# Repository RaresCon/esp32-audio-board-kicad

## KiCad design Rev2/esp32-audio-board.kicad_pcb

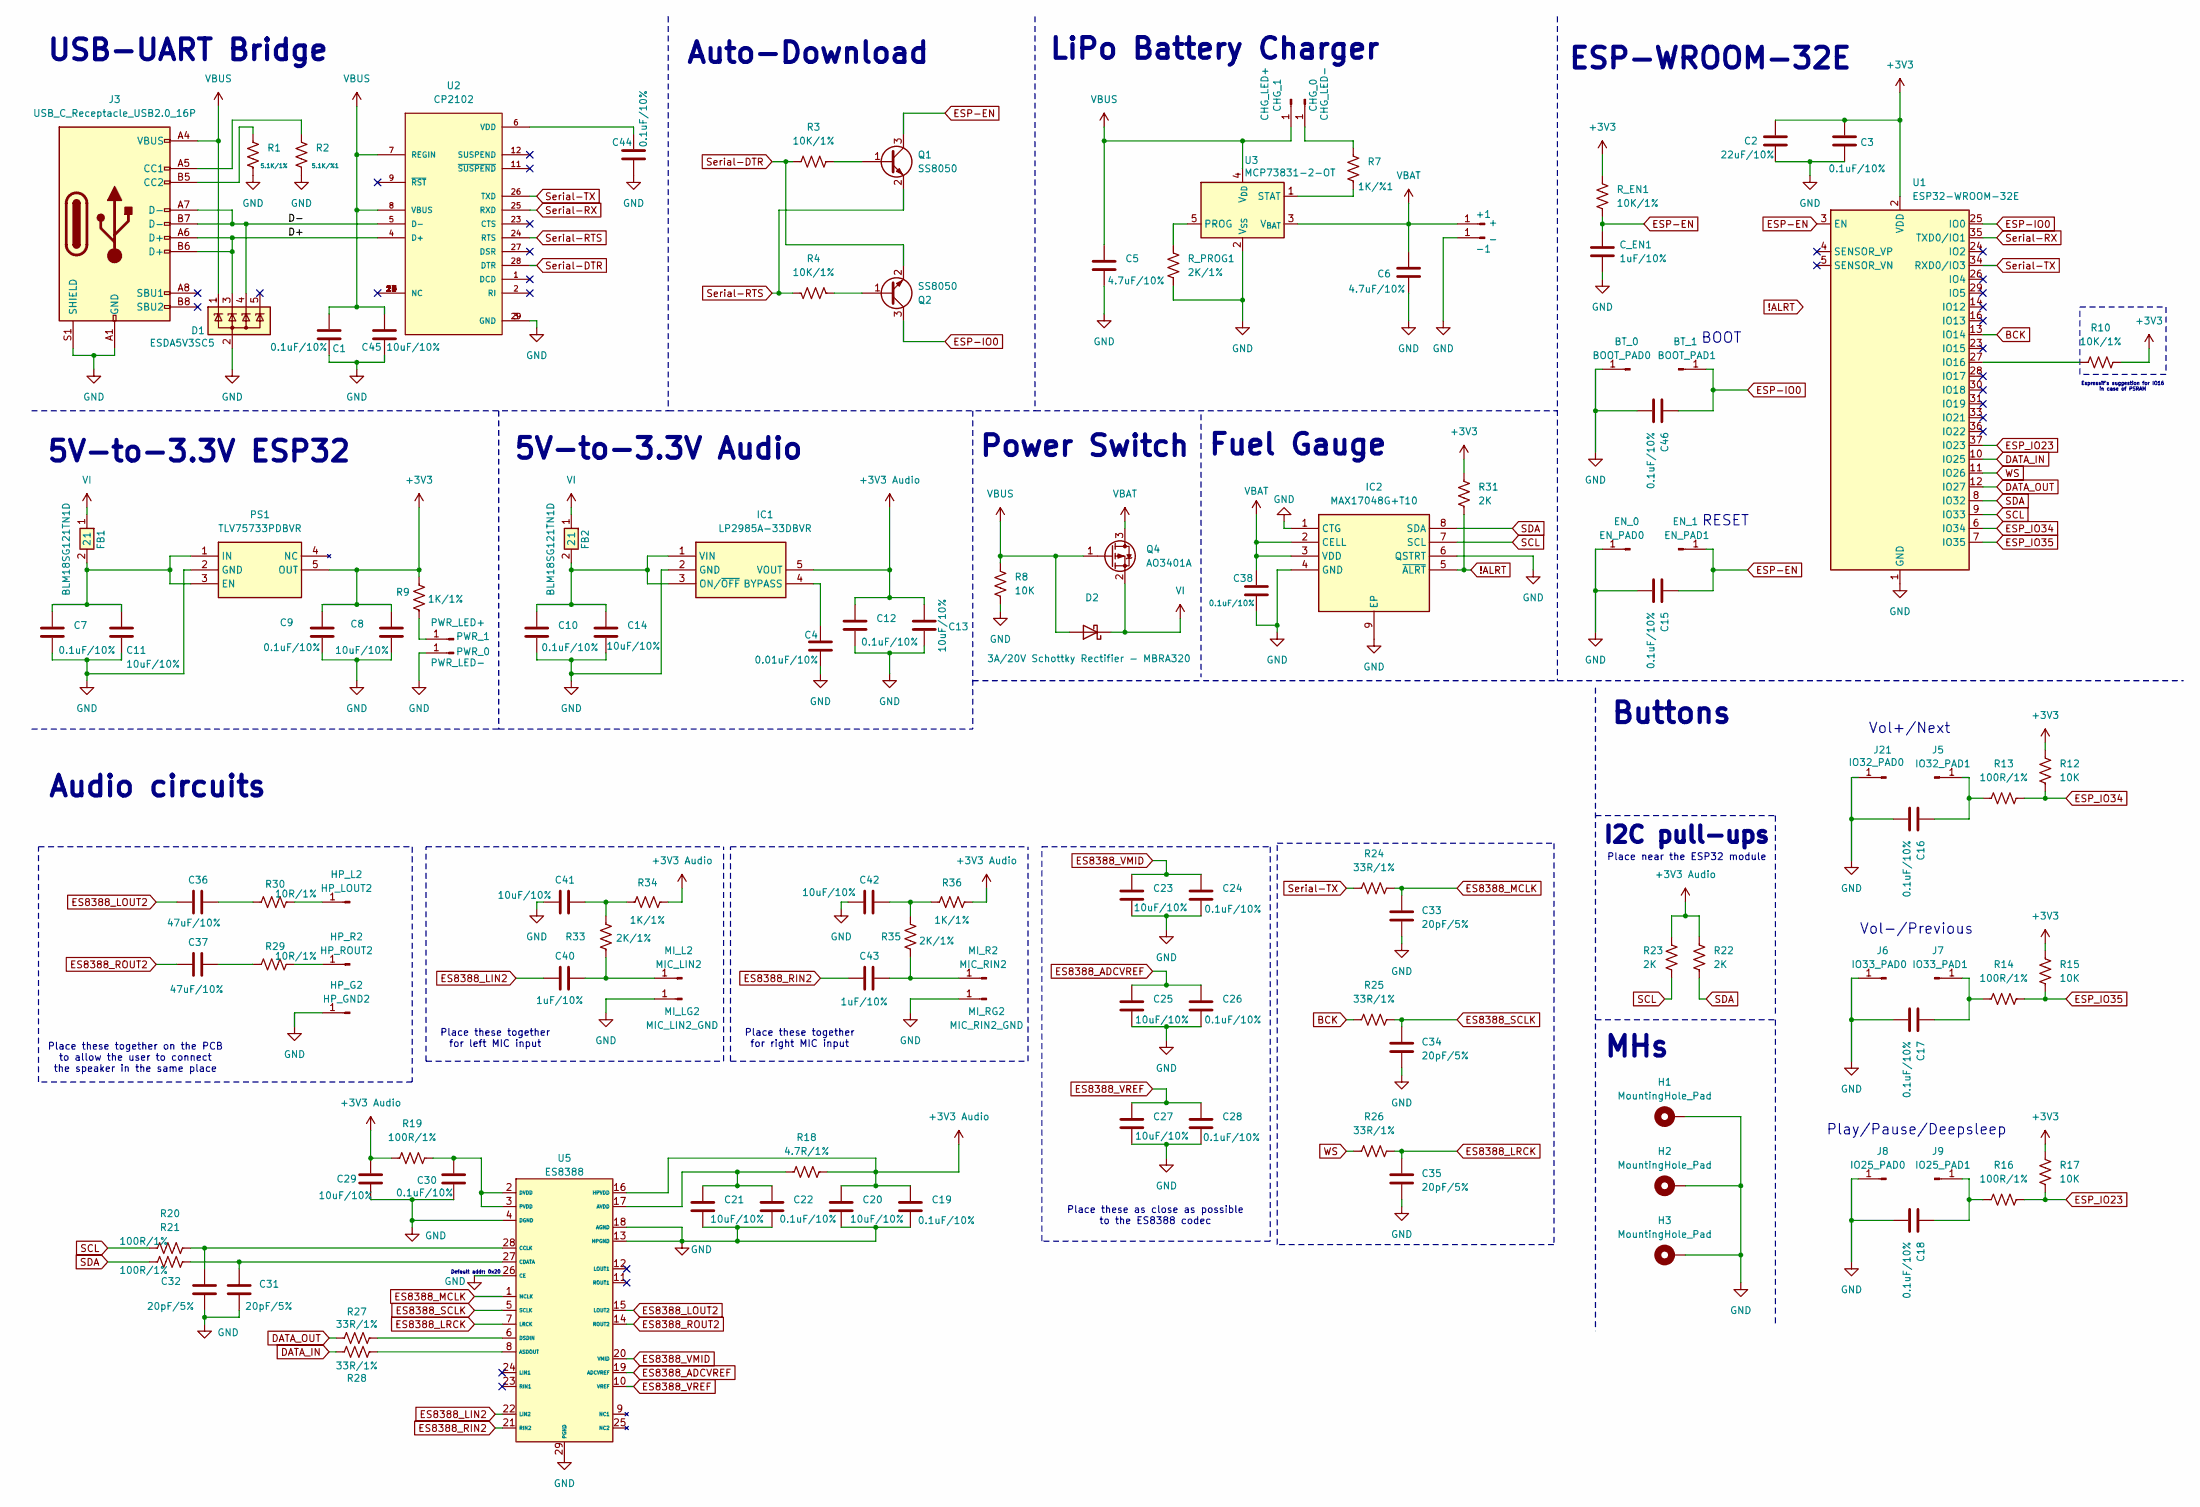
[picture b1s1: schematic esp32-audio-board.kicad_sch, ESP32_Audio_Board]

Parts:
+1: +; SolderPad_SMD_2x2mm
-1: -; SolderPad_SMD_2x2mm
BT_0: BOOT_PAD0; SolderPad_SMD_1x1mm
BT_1: BOOT_PAD1; SolderPad_SMD_1x1mm
C1, C3, C7, C9, C10, C12, C15, C16, C17, C18, C19, C22, C24, C26, C28, C30, C38, C44, C46: 0.1uF/10%; C_0402_1005Metric_Pad0.74x0.62mm_HandSolder
C2: 22uF/10%; C_0402_1005Metric_Pad0.74x0.62mm_HandSolder
C4: 0.01uF/10%; C_0402_1005Metric_Pad0.74x0.62mm_HandSolder
C5, C6: 4.7uF/10%; C_0402_1005Metric_Pad0.74x0.62mm_HandSolder
C8, C11, C13, C14, C20, C21, C23, C25, C27, C29, C41, C42, C45: 10uF/10%; C_0402_1005Metric_Pad0.74x0.62mm_HandSolder
C31, C32, C33, C34, C35: 20pF/5%; C_0402_1005Metric_Pad0.74x0.62mm_HandSolder
C36, C37: 47uF/10%; C_0402_1005Metric_Pad0.74x0.62mm_HandSolder
C40, C43: 1uF/10%; C_0402_1005Metric_Pad0.74x0.62mm_HandSolder
CHG_0: CHG_LED-; SolderPad_SMD_1x1mm
CHG_1: CHG_LED+; SolderPad_SMD_1x1mm
C_EN1: 1uF/10%; C_0402_1005Metric_Pad0.74x0.62mm_HandSolder
D1: ESDA5V3SC5; SOT-23-5_HandSoldering
D2: 3A/20V Schottky Rectifier - MBRA320; D_SMA
EN_0: EN_PAD0; SolderPad_SMD_1x1mm
EN_1: EN_PAD1; SolderPad_SMD_1x1mm
FB1, FB2: BLM18SG121TN1D; BLM18EG101TH1D; Mouser Part Number 81-BLM18SG121TN1D
H1, H2, H3: MountingHole_Pad; MountingHole_2.2mm_M2_Pad_TopOnly
HP_G2: HP_GND2; SolderPad_SMD_1x2mm
HP_L2: HP_LOUT2; SolderPad_SMD_1x2mm
HP_R2: HP_ROUT2; SolderPad_SMD_1x2mm
IC1: LP2985A-33DBVR; SOT95P280X145-5N; Mouser Part Number 595-LP2985A-33DBVR
IC2: MAX17048G+T10; SON50P200X200X80-9N-D; Mouser Part Number 700-MAX17048G+T10
J3: USB_C_Receptacle_USB2.0_16P; USB_C_Receptacle_GCT_USB4105-xx-A_16P_TopMnt_Horizontal
J5: IO32_PAD1; SolderPad_SMD_1x1mm
J6: IO33_PAD0; SolderPad_SMD_1x1mm
J7: IO33_PAD1; SolderPad_SMD_1x1mm
J8: IO25_PAD0; SolderPad_SMD_1x1mm
J9: IO25_PAD1; SolderPad_SMD_1x1mm
J21: IO32_PAD0; SolderPad_SMD_1x1mm
MI_L2: MIC_LIN2; SolderPad_SMD_1x2mm
MI_LG2: MIC_LIN2_GND; SolderPad_SMD_1x2mm
MI_R2: MIC_RIN2; SolderPad_SMD_1x2mm
MI_RG2: MIC_RIN2_GND; SolderPad_SMD_1x2mm
PS1: TLV75733PDBVR; SOT95P280X145-5N; Mouser Part Number 595-TLV75733PDBVR
PWR_0: PWR_LED-; SolderPad_SMD_1x1mm
PWR_1: PWR_LED+; SolderPad_SMD_1x1mm
Q1, Q2: SS8050; SOT-23
Q4: AO3401A; SOT-23
R1: 5.1K/1%; R_0402_1005Metric_Pad0.72x0.64mm_HandSolder
R2: 5.1K/%1; R_0402_1005Metric_Pad0.72x0.64mm_HandSolder
R3, R4, R10: 10K/1%; R_0402_1005Metric_Pad0.72x0.64mm_HandSolder
R7: 1K/%1; R_0402_1005Metric_Pad0.72x0.64mm_HandSolder
R8, R12, R15, R17: 10K; R_0402_1005Metric_Pad0.72x0.64mm_HandSolder
R9, R34, R36: 1K/1%; R_0402_1005Metric_Pad0.72x0.64mm_HandSolder
R13, R14, R16, R19, R20, R21: 100R/1%; R_0402_1005Metric_Pad0.72x0.64mm_HandSolder
R18: 4.7R/1%; R_0402_1005Metric_Pad0.72x0.64mm_HandSolder
R22, R23, R31: 2K; R_0402_1005Metric_Pad0.72x0.64mm_HandSolder
R24, R25, R26, R27, R28: 33R/1%; R_0402_1005Metric_Pad0.72x0.64mm_HandSolder
R29, R30: 10R/1%; R_0402_1005Metric_Pad0.72x0.64mm_HandSolder
R33, R35: 2K/1%; R_0402_1005Metric_Pad0.72x0.64mm_HandSolder
R_EN1: 10K/1%; R_0402_1005Metric_Pad0.72x0.64mm_HandSolder
R_PROG1: 2K/1%; R_0402_1005Metric_Pad0.72x0.64mm_HandSolder
U1: ESP32-WROOM-32E
U2: CP2102; QFN50P500X500X100-29N
U3: MCP73831-2-OT; SOT-23-5
U5: ES8388; QFN-28-1EP_4x4mm_P0.45mm_EP2.6x2.6mm

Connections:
!ALRT: IC2.5 (~ALRT), R31.2
+3V3: C2.1, C3.1, C8.1, C9.1, PS1.5 (OUT), R9.2, R10.2, R12.2, R15.2, R17.2, R31.1, R_EN1.1, U1.2 (VDD)
+3V3 Audio: C12.1, C13.1, C19.1, C20.1, C29.1, IC1.5 (VOUT), R18.2, R19.1, R22.1, R23.1, R34.2, R36.2, U5.16 (HPVDD)
/D+: D1.3 (K), J3.A6 (D+), J3.B6 (D+), U2.4 (D+)
/D-: D1.4 (K), J3.A7 (D-), J3.B7 (D-), U2.5 (D-)
BCK: R25.1, U1.13 (IO14)
DATA_IN: R28.1, U1.10 (IO25)
DATA_OUT: R27.1, U1.12 (IO27)
ES8388_ADCVREF: C25.1, C26.1, U5.19 (ADCVREF)
ES8388_LIN2: C40.1, U5.22 (LIN2)
ES8388_LOUT2: C36.1, U5.15 (LOUT2)
ES8388_LRCK: C35.1, R26.2, U5.7 (LRCK)
ES8388_MCLK: C33.1, R24.2, U5.1 (MCLK)
ES8388_RIN2: C43.1, U5.21 (RIN2)
ES8388_ROUT2: C37.1, U5.14 (ROUT2)
ES8388_SCLK: C34.1, R25.2, U5.5 (SCLK)
ES8388_VMID: C23.1, C24.1, U5.20 (VMID)
ES8388_VREF: C27.1, C28.1, U5.10 (VREF)
ESP-EN: C15.1, C_EN1.1, EN_1.1 (Pin_1_1), Q1.3 (C), R_EN1.2, U1.3 (EN)
ESP-IO0: BT_1.1 (Pin_1_1), C46.1, Q2.3 (C), U1.25 (IO0)
ESP_IO23: R16.1, R17.1, U1.37 (IO23)
ESP_IO34: R12.1, R13.1, U1.6 (IO34)
ESP_IO35: R14.1, R15.1, U1.7 (IO35)
GND: -1.1 (Pin_1_1), BT_0.1 (Pin_1_1), C1.2, C2.2, C3.2, C4.2, C5.2, C6.2, C7.2, C8.2, C9.2, C10.2, C11.2, C12.2, C13.2, C14.2, C15.2, C16.2, C17.2, C18.2, C19.2, C20.2, C21.2, C22.2, C23.2, C24.2, C25.2, C26.2, C27.2, C28.2, C29.2, C30.2, C31.2, C32.2, C33.2, C34.2, C35.2, C38.2, C41.1, C42.1, C44.2, C45.2, C46.2, C_EN1.2, D1.2 (A), EN_0.1 (Pin_1_1), H1.1 (1_1), H2.1 (1_1), H3.1 (1_1), HP_G2.1 (Pin_1_1), IC1.2 (GND), IC2.1 (CTG), IC2.4 (GND), IC2.6 (QSTRT), IC2.9 (EP), J3.A1 (GND), J3.A12 (GND), J3.B1 (GND), J3.B12 (GND), J3.S1 (SHIELD), J6.1 (Pin_1_1), J8.1 (Pin_1_1), J21.1 (Pin_1_1), MI_LG2.1 (Pin_1_1), MI_RG2.1 (Pin_1_1), PS1.2 (GND), PWR_0.1 (Pin_1_1), R1.2, R2.2, R8.1, R_PROG1.2, U1.1 (GND), U1.15 (GND), U1.38 (GND), U1.39 (GND), U2.3 (GND), U2.29 (GND), U3.2 (V_{SS}), U5.4 (DGND), U5.13 (HPGND), U5.18 (AGND), U5.26 (CE), U5.29 (PGND)
unnamed: C36.2, R30.1
unnamed: C37.2, R29.1
unnamed: C41.2, R33.2, R34.1
unnamed: C42.2, R35.2, R36.1
unnamed: CHG_0.1 (Pin_1_1), R7.2
unnamed: HP_L2.1 (Pin_1_1), R30.2
unnamed: HP_R2.1 (Pin_1_1), R29.2
unnamed: C4.1, IC1.4 (BYPASS)
unnamed: C10.1, C14.1, FB2.2, IC1.1 (VIN), IC1.3 (ON/~OFF)
unnamed: J3.A5 (CC1), R2.1
unnamed: J3.B5 (CC2), R1.1
unnamed: C16.1, J5.1 (Pin_1_1), R13.2
unnamed: C17.1, J7.1 (Pin_1_1), R14.2
unnamed: C18.1, J9.1 (Pin_1_1), R16.2
unnamed: C40.2, MI_L2.1 (Pin_1_1), R33.1
unnamed: C43.2, MI_R2.1 (Pin_1_1), R35.1
unnamed: C7.1, C11.1, FB1.2, PS1.1 (IN), PS1.3 (EN)
unnamed: PWR_1.1 (Pin_1_1), R9.1
unnamed: Q1.1 (B), R3.2
unnamed: Q2.1 (B), R4.1
unnamed: R10.1, U1.27 (IO16)
unnamed: C44.1, U2.6 (VDD)
unnamed: R_PROG1.1, U3.5 (PROG)
unnamed: R7.1, U3.1 (STAT)
unnamed: R28.2, U5.8 (ASDOUT)
unnamed: C21.1, C22.1, R18.1, U5.17 (AVDD)
unnamed: C32.1, R20.2, U5.28 (CCLK)
unnamed: C31.1, R21.2, U5.27 (CDATA)
unnamed: R27.2, U5.6 (DSDIN)
unnamed: C30.1, R19.2, U5.2 (DVDD), U5.3 (PVDD)
SCL: IC2.7 (SCL), R20.1, R23.2, U1.9 (IO33)
SDA: IC2.8 (SDA), R21.1, R22.2, U1.8 (IO32)
Serial-DTR: Q2.2 (E), R3.1, U2.28 (DTR)
Serial-RTS: Q1.2 (E), R4.2, U2.24 (RTS)
Serial-RX: U1.35 (TXD0/IO1), U2.25 (RXD)
Serial-TX: R24.1, U1.34 (RXD0/IO3), U2.26 (TXD)
VBAT: +1.1 (Pin_1_1), C6.1, C38.1, IC2.2 (CELL), IC2.3 (VDD), Q4.3 (D), U3.3 (V_{BAT})
VBUS: C1.1, C5.1, C45.1, CHG_1.1 (Pin_1_1), D1.1 (K), D2.2 (A), J3.A4 (VBUS), J3.A9 (VBUS), J3.B4 (VBUS), J3.B9 (VBUS), Q4.1 (G), R8.2, U2.7 (REGIN), U2.8 (VBUS), U3.4 (V_{DD})
VI: D2.1 (K), FB1.1, FB2.1, Q4.2 (S)
WS: R26.1, U1.11 (IO26)

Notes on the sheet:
Place these together for left MIC input
I2C pull-ups
5V-to-3.3V ESP32
Place these together for right MIC input
Place these as close as possible to the ES8388 codec
Vol+/Next
Audio circuits
Auto-Download
BOOT
Play/Pause/Deepsleep
USB-UART Bridge
MHs
LiPo Battery Charger
Fuel Gauge
RESET
Place near the ESP32 module
5V-to-3.3V Audio
Default addr: 0x20
Place these together on the PCB to allow the user to connect the speaker in the same place
Espressif's suggestion for IO16 in case of PSRAM
Buttons
ESP-WROOM-32E
Vol-/Previous
Power Switch

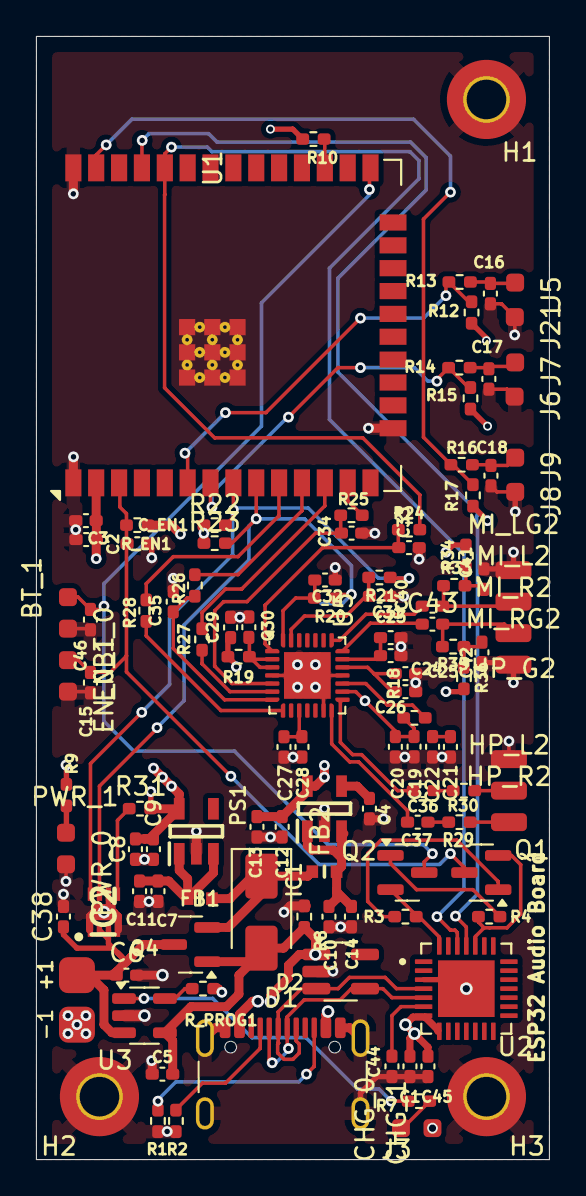
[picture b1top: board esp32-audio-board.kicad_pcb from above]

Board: 4 copper layers, 28.5 x 62.4 mm, 121 parts (0 on the bottom side), 64 nets.

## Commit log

2025-03-05 esp32-audio-board: init schematic
    Added schematic for the ESP32-Audio-Board project.
    Added the initial USB-UART interface and the auto-download circuit.
2025-03-07 esp32-audio-board: add power supplies
    Added the LiPo battery charger and the USB/battery
    power switch that will allow the battery to charge
    without powering the ESP module. The battery still
    powers the audio components while charging.
    Added two power LDOs that will supply the ESP32 module
    and other functional ICs separate from the audio module.
2025-03-08 esp32-audio-board: add function buttons
    Added four buttons, one for resetting the ESP32 module
    and other three for audio functions like volume up/down,
    play/pause and next/prev.
2025-03-09 esp32-audio-board: add ES8388 codec
    Added the ES8388 codec and all the needed circuits to
    allow the user to hook up any speaker they want to some
    pads on the PCB.
2025-03-09 esp32-audio-board: small improvements
    Added some small improvements on the schematic to be easier
    to understand before continuing to PCB design.
2025-03-10 esp32-audio-board: PCB design and change LDOs
    Added the initial position of the components on the board,
    the button and input pads need to be placed on the outer
    part of the PCB.
    Changed the LDOs to XC6220A331 to allow for a lower DO
    voltage, which would occur while using the battery.
2025-03-11 esp32-audio-board: add ferrite beads on pwr lanes
    Added two ferrite beads (BLM) on the high power
    rails - from USB-C/battery, to lower the EMI.
    Added some little improvements to the schematic and PCB.
2025-03-11 esp32-audio-board: rehook ES8388
    Rehooked the ES8388 to allow the routing to be
    easier and allow ground planes under the I2C and
    I2S to limit EMI and noise.
2025-03-11 esp32-audio-board: route initial power
    Added routing for the USB-C and battery initial
    lanes/traces to also see how small the PCB can
    be as width.
2025-03-14 esp32-audio-board: complete PCB general design
    Added the initial PCB complete design.
    Changed the CH340C with CP2102 to allow the board to
    consume less energy while not connected to USB.
2025-03-17 esp32-audio-board: complete PCB
    Added all the pads and connections for external input
    and output. Made the board smaller to allow the case
    to be slimmer.
2025-03-18 esp32-audio-board: PCB improvements
    Rerouted the buttons pins to not use the SENSOR_VN
    and SENSOR_VP pins, avoiding any problems with not
    being able to pull-up/down them. Added all the
    silkscreen texts and reduced the DRC warnings to 1
    (silkscreen overlap).
2025-03-19 esp32-audio-board: add initial README
    Added the initial README, which includes the schematic
    hookup between ESP-WROOM-32E and ES8388/CP2102.
2025-03-22 esp32-audio-board: power changes
    Changed the LDOs to make the PCB more power
    efficient and try to find these parts in stock.
    Changed the footprint for the Q4 to be more compact.
2025-03-22 esp32-audio-board: fix GND plane for EN cap
    The capacitor close to the ESP module was cutting
    the GND pour narrow to about 0.3mm, which can be
    too narrow for a stable GND signal to pass. Moved
    some traces around it and added many GND viases for
    caps and resistors to allow for shorter GND routes.
2025-03-25 esp32-audio-board: refactor PCB
    Added many changes to the PCB, which hopefully
    will protect the PCB from EMI even better and
    will ensure that all signals have a short return
    path to GND plane. Added pads for a boot button
    to allow the board to be flashed even if the
    auto-download circuit will not work.
2025-03-26 esp32-audio-board: add bigger pads for pins
    Added two new pads for audio pins and button pins
    to allow larger cables to be soldered to the board.
2025-03-26 esp32-audio-board: add testpoints and tweaks
    Added testpoints for SDA/SCL lines to allow for
    rising edge refinements if needed for ES8388.
    Checked all the decoupling capacitors and viases
    for mistakes, fixed (hopefully) all of them.
    Sent the board in production!
2025-04-05 esp32-audio-board: fix VI for audio pwr
    The audio 3V3 was coming directly from the battery, which
    may not be present and the VBUS should power the audio
    circuits. The production board has this problem, but it
    should not be affected if a battery is plugged in, as
    the battery voltage will be present and the battery will
    power the audio circuits correctly even when charging.
2026-05-14 esp32-audio-board: add initial commit for 2nd rev
    Moved the 1st rev files to a new directory and duplicated it where the
    2nd rev will be worked on.
2026-05-14 esp32-audio-board: add initial Rev2 schematic
    Added an initial Rev2 schematic that contains all the main
    components, except the connector to the sense board. This
    can be decided later.
2026-05-16 esp32-audio-board: initial Rev2 PCB
    Started working on the Rev2 PCB. Managed to get components
    a lot closer and the PCB layout is more compact. The PCB
    width got smaller by ~10mm.
2026-05-17 esp32-audio-board: Rev2 PCB done
    Completed the work on the Rev2 PCB.
